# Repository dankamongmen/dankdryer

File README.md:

<p align="center">
ESP32, OpenSCAD, and KiCad sources for the Dankdryer, the world's best filament dryer.
 
 a nick black joint
</p>

# Features

* Temperatures up to at least 150℃  when printed with proper materials.
  * Such temperatures are appropriate (necessary) for certain engineering filaments.
  * A high-temperature spool is required at these temperatures.
* Accurate weight sensing throughout to determine how much water has been exorcised.
  * Post contextless deltas to reddit in the heat of dumbass arguments! DATA, bitch!
* Slow rotation like delicious savory meat.
* Equal heating of all the spool's filament.
* Control and reporting over MQTT via WiFi.
* OTA firmware upgrades.
* Isolated hot and cool chambers, with most active equipment in the cool chamber.
* Humidity sensing and temperature sensing in both chambers.
* Entirely open source.

More info at [dankwiki](https://nick-black.com/dankwiki/index.php/Dankdryer).

# Dependencies

The project is built with GNU Make.
Running `make` in the toplevel will attempt to build firmware and STLs.
Building the firmware requires the `esp-idf` library and a configured
ESP-IDF environment (i.e. the various `IDF_*` environment variables
must be set), along with CMake. `idf.py` ought be in your `$PATH`,
and work when invoked.

## Firmware
* [esp-idf](https://github.com/espressif/esp-idf) 5.3+
* [CMake](https://gitlab.kitware.com/cmake/cmake) 3.16+

## 3D models
* OpenSCAD 2024.10+

I use
[BOSL2](https://github.com/BelfrySCAD/BOSL2), which
is included as a submodule.

## PCB
* KiCad 8+

# Construction / BOM

The device as designed requires approximately 600g of high-temperature filament
(PA6-CF, PA6-GF, PAHT-CF, etc.) to print. The exact amount of filament will
depend on material and print settings. Six pieces must
be printed:

 * Hot chamber
 * Cool chamber
 * Top
 * Motor sheath
 * Sheath coupling
 * Spool platform

The hot and cool chamber dominate filament consumption, though the top is
non-negligible.

### Hot chamber

* [230C 110V ceramic heating element](https://www.amazon.com/dp/B0BXNPXXYW)
* [KSD301 175C NC thermal control](https://www.aliexpress.us/item/2251832675942217.html)
* [Hall sensor](https://www.digikey.com/en/products/detail/diodes-incorporated/AH3712Q-P-B/19920700)
* Custom PCB (fabrication cost is negligible; see components below)

We need a temperature sensor and hall effect sensor (and obviously the
heating circuit) in the hot box; nothing else ought be there.

### Cool chamber

* [Greartisan 5RPM 12V DC motor](https://www.amazon.com/dp/B072N867G3/)
* [NEMA plug + rocker switch](https://www.amazon.com/ASHATA-Rocker-Switch-Adapter-Printer/dp/B085VSS1F2)
* [160W 12V AC adapter](https://www.amazon.com/gp/product/B0D7GMVK2F)
* [8dBi antenna](https://www.aliexpress.us/item/3256807262687553.html)
* 5kg bar strain load cell
* 2-to-4 cable splitter
* Custom PCB (fabrication cost is negligible; see components below)

#### PCB components

Generated via Kicad:

|Designator|Footprint|Quantity|Designation|
|----------|---------|--------|-----------|
|U1|TPS62132|1|TPS62132|
|R4|R_1206_3216Metric_Pad1.30x1.75mm_HandSolder|1|360|
|R2|R_1206_3216Metric_Pad1.30x1.75mm_HandSolder|1|620|
|R6,R8|R_1206_3216Metric_Pad1.30x1.75mm_HandSolder|2|4.7k|
|C15,C16|C_1206_3216Metric_Pad1.33x1.80mm_HandSolder|2|1n|
|SW2|SW_B3F-1000_OMR|1|bootmode|
|R13,R20,R15|R_1206_3216Metric_Pad1.30x1.75mm_HandSolder|3|10k|
|R5,R1,R22|R_1206_3216Metric_Pad1.30x1.75mm_HandSolder|3|680|
|C7,C3,C9,C8,C20|C_1206_3216Metric_Pad1.33x1.80mm_HandSolder|5|0.1u|
|U2|TRANS_AH3712-P-B_DIO|1|AH3712Q-P-B|
|C6,C13|C_1206_3216Metric_Pad1.33x1.80mm_HandSolder|2|22u|
|C10,C17|C_1206_3216Metric_Pad1.33x1.80mm_HandSolder|2|1u|
|IC1|DIP792W51P254L1905H53Q16N|1|NAU7802KGI|
|J10|FanPinHeader_1x04_P2.54mm_Vertical|1|lower fan|
|C19,C2,C1,C14|C_1206_3216Metric_Pad1.33x1.80mm_HandSolder|4|10u|
|J2|JST_VH_B5P-VH-B_1x05_P3.96mm_Vertical|1|to microboard|
|J4|TerminalBlock_bornier-2_P5.08mm|1|heater|
|J8|TerminalBlock_bornier-2_P5.08mm|1|motor|
|J7|FanPinHeader_1x04_P2.54mm_Vertical|1|upper fan|
|R9,R19|R_1206_3216Metric_Pad1.30x1.75mm|2|15k|
|U6|XCVR_ESP32-C6-MINI-1U-H4|1|ESP32-C6-MINI-1U|
|J11|PinHeader_1x01_P1.00mm_Vertical|1|testpin|
|R16|R_1206_3216Metric_Pad1.30x1.75mm_HandSolder|1|412|
|J13|BarrelJack_Wuerth_6941xx301002|1|barreljack|
|R7|R_1206_3216Metric_Pad1.30x1.75mm_HandSolder|1|1.62k|
|C4,C18|C_1206_3216Metric_Pad1.33x1.80mm_HandSolder|2|.01u|
|J5|TerminalBlock_bornier-4_P5.08mm|1|5kg load cell|
|R10,R11|R_0805_2012Metric_Pad1.15x1.40mm_HandSolder|2|47|
|U5|TO-92_Inline|1|LM35-LP|
|R3|R_1206_3216Metric_Pad1.30x1.75mm_HandSolder|1|100|
|L1|IND_IFSC_1515AH_VIS|1|2.2u|
|R14|R_1206_3216Metric_Pad1.30x1.75mm_HandSolder|1|3.3k|
|OC1|MOC306XS_LTO|1|MOC3063S|
|C12|C_1206_3216Metric_Pad1.33x1.80mm_HandSolder|1|3.3n|
|C11|C_0805_2012Metric_Pad1.18x1.45mm_HandSolder|1|470p|
|R21|R_1206_3216Metric_Pad1.30x1.75mm_HandSolder|1|68|
|J9|PinHeader_1x04_P2.54mm_Vertical|1|UART|
|J6|JST_PHD_B8B-PHDSS_2x04_P2.00mm_Vertical|1|LCD|
|J3|JST_VH_B5P-VH-B_1x05_P3.96mm_Vertical|1|to baseboard|
|Q3|TO-263-2|1|T1210-800G|
|Q2|SOT-323_SC-70|1|SSM3K127TU|
|R12|R_1206_3216Metric_Pad1.30x1.75mm_HandSolder|1|330|
|U3|SOT-89-3|1|HT7550|

# MQTT

MQTT is used to report status and to accept commands.

## Controls

* `NAME/control/tare`: tare using the last weight read
* `NAME/control/dry`: takes as argument a string "DRYS/TEMP", where DRYS and TEMP are unsigned integers
    specifying the number of seconds to dry, and the temperature to dry at. Any ongoing drying operation
    will be replaced with the newly specified one. Specifying zero for DRYS will cancel any ongoing
    drying operation.
* `NAME/control/lpwm`: takes as argument a hexadecimal number between 0 and 255, left-padded with zeroes
    so as to be exactly two digits, i.e. "00".."ff". Sets the lower fan's PWM.
* `NAME/control/upwm`: takes as argument a hexadecimal number between 0 and 255, left-padded with zeroes
    so as to be exactly two digits, i.e. "00".."ff". Sets the upper fan's PWM.
* `NAME/control/factoryreset`: takes no arguments. Blanks the persistent storage, disables the motor
    and heater, and reboots.

# Renderings

View from the top of the lower chamber by itself, with the AC
adapter and motor assembly present.

Combined OpenSCAD render for mating testing.

# Questions

* How does air flow? Let's get some visible air and test it.
* What all could we accomplish by reading RFID?

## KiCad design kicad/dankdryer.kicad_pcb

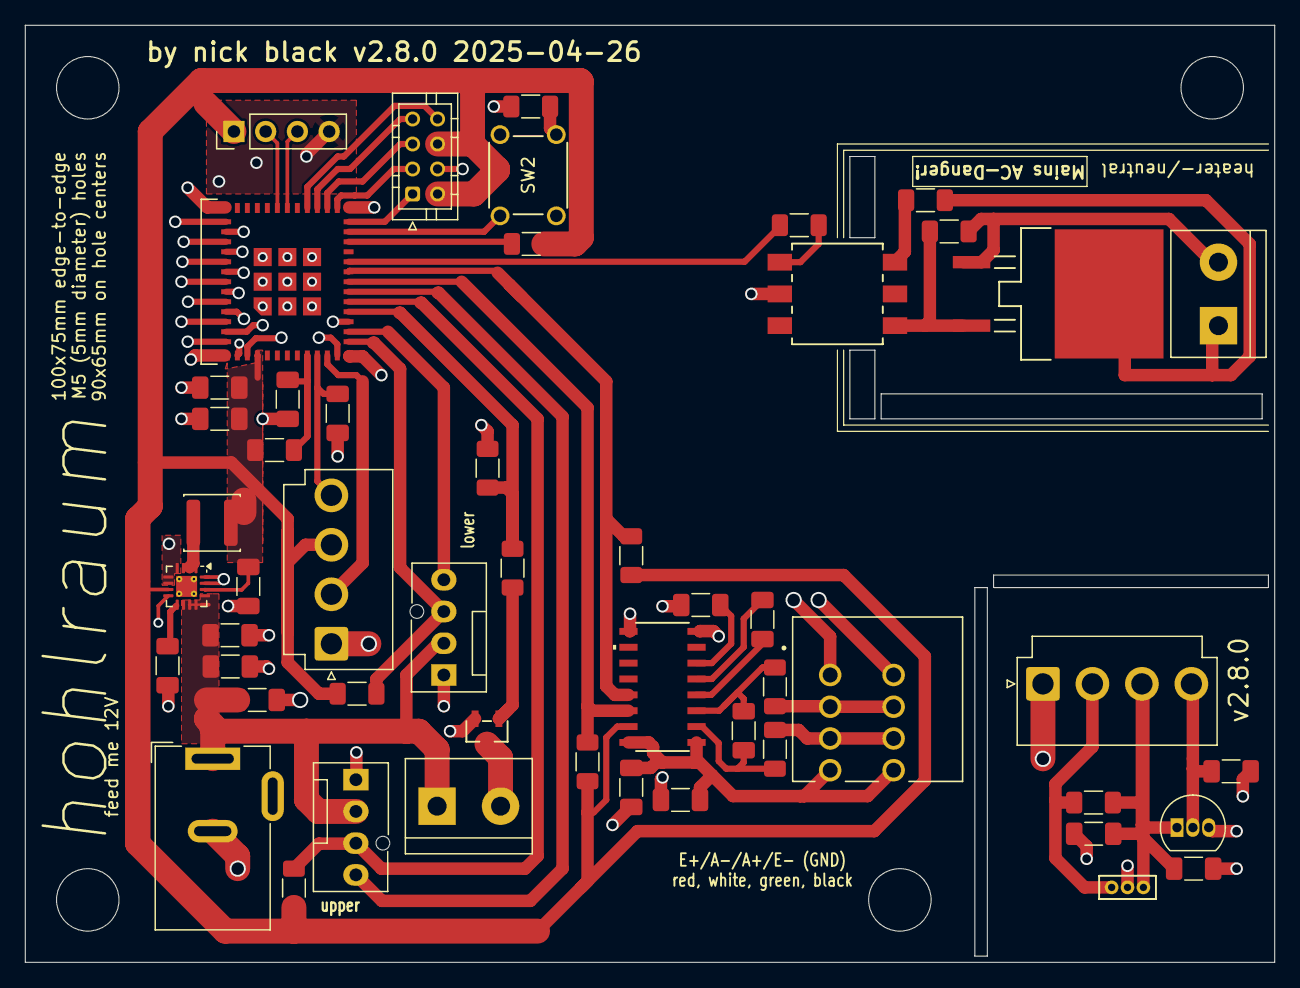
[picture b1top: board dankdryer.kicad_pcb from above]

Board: 2 copper layers, 100.0 x 75.0 mm, 52 parts (0 on the bottom side), 44 nets.

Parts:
C1, C14, C19: 10u; C_1206_3216Metric_Pad1.33x1.80mm_HandSolder
C2, C3, C5, C8, C9, C20: 100n; C_1206_3216Metric_Pad1.33x1.80mm_HandSolder
C4: 10n; C_1206_3216Metric_Pad1.33x1.80mm_HandSolder
C6, C21: 22u; C_1206_3216Metric_Pad1.33x1.80mm_HandSolder
C7: 3.3n; C_1206_3216Metric_Pad1.33x1.80mm_HandSolder
C10, C12, C17: 1u; C_1206_3216Metric_Pad1.33x1.80mm_HandSolder
C11: 330p; C_1206_3216Metric_Pad1.33x1.80mm_HandSolder
D1: T1210-800G-TR
J1: 1-2834016-4; TE_1-2834016-4
J2: to microboard; JST_VH_B4P-VH-B_1x04_P3.96mm_Vertical
J3: to baseboard; JST_VH_B4P-VH-B_1x04_P3.96mm_Vertical
J4, J8: ScrewX2; TerminalBlock_bornier-2_P5.08mm
J6: LCD; JST_PHD_B8B-PHDSS_2x04_P2.00mm_Vertical
J7, J10: HeaderX4; FanPinHeader_1x04_P2.54mm_Vertical
J9: UART; PinHeader_1x04_P2.54mm_Vertical
J13: barreljack; BarrelJack_Wuerth_6941xx301002
L1: 2.2u; L_Sunlord_SWPA4030S
OC1: MOC3063SM; MOC306XS_LTO
Q1: AH3712-P-B; TRANS_AH3712-P-B_DIO
Q2: IRLML2502TRPbF; IRLML2502TRPBF
R1, R5: 680; R_1206_3216Metric_Pad1.30x1.75mm_HandSolder
R2, R12: 330; R_1206_3216Metric_Pad1.30x1.75mm_HandSolder
R3: 100; R_1206_3216Metric_Pad1.30x1.75mm_HandSolder
R4: 390; R_1206_3216Metric_Pad1.30x1.75mm_HandSolder
R6, R8: 2.2k; R_1206_3216Metric_Pad1.30x1.75mm_HandSolder
R7, R13, R15, R20: 10k; R_1206_3216Metric_Pad1.30x1.75mm_HandSolder
R10, R11: 47; R_1206_3216Metric_Pad1.30x1.75mm_HandSolder
R14: 3.3k; R_1206_3216Metric_Pad1.30x1.75mm_HandSolder
SW2: boot; SW_B3F-1000_OMR
U3: NAU7802SGI; SOI16_NAU7802SGI_NUV
U4: TPS62132RGTR; VQFN-16-1EP_3x3mm_P0.5mm_EP1.68x1.68mm_ThermalVias
U5: LMT87LPM; TO-92_Inline
U6: ESP32-C6-MINI-1U; ESP32-C6-MINI-1U-H4

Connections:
+3.3V: C3.1, C6.2, C21.1, J2.3, J6.2, J6.6, J9.1, L1.2, R1.1, R5.1, R6.1, R8.1, R13.1, R15.1, U3.15 (DVDD), U4.7 (FSW), U4.14 (VOS), U6.3 (3V3)
+3.3Vmicro: C4.2, C19.2, J3.3, Q1.1 (VDD), R20.1, U5.1 (+V_{S})
+12V: C1.1, C2.2, C14.1, J7.2, J8.1, J10.2, J13.1, U4.10 (AVIN), U4.11 (PVIN), U4.12 (PVIN__1), U4.13 (EN)
/ACNeutral: D1.1 (A1), J4.2, R4.2
/BootDown: R15.2, U6.22 (IO8)
/BootSPI: SW2.1, U6.23 (IO9)
/Hall: J2.2, U6.10 (IO5)
/HeaterNeutral: D1.3 (A2), J4.1, R3.2
/LPWM: J10.4, U6.13 (IO1)
/LTach: J10.3, R5.2, U6.12 (IO0)
/Microboard/HallMicro: J3.2, Q1.3 (OUTPUT), R20.2
/Microboard/ThermMicro: C17.2, J3.4, U5.2 (V_{OUT})
/Motor: R7.1, R12.1, U6.15 (IO6)
/RXD0: J9.3, U6.30 (RXD0)
/SCL: R6.2, U3.13 (SCLK), U6.19 (IO14)
/SDA: R8.2, U3.14 (SDIO), U6.18 (IO13)
/SSRControl: R2.2, U6.20 (IO15)
/TXD0: J9.2, U6.31 (TXD0)
/Therm: C20.1, J2.4, U6.9 (IO4)
/UPWM: J7.4, U6.17 (IO12)
/UTach: J7.3, R1.2, U6.16 (IO7)
A+: J1.2_1 (2), J1.2_2 (2__1), R11.1
A-: J1.3_1 (3), J1.3_2 (3__1), R10.1
E+: C5.1, C12.1, J1.4_1 (4), J1.4_2 (4__1), U3.1 (REFP), U3.16 (AVDD/LDO)
GND: C1.2, C2.1, C3.2, C4.1, C5.2, C6.1, C7.2, C8.2, C10.2, C12.2, C14.2, C17.1, C19.1, C20.2, C21.2, J1.1_1 (1), J1.1_2 (1__1), J2.1, J3.1, J6.4, J7.1, J9.4, J10.1, J13.2, OC1.2 (C), Q1.2 (GND), Q2.2 (S), R7.2, R14.2, U3.8 (AVSS), U3.9 (DVSS), U4.4 (PG), U4.5 (FB), U4.6 (AGND), U4.8 (DEF), U4.15 (PGND), U4.16 (PGND__1), U4.17 (PGND__2), U5.3 (GND), U6.1 (GND1), U6.2 (GND1), U6.11 (GND1), U6.14 (GND1), U6.36 (GND1), U6.37 (GND1), U6.38 (GND1), U6.39 (GND1), U6.40 (GND1), U6.41 (GND1), U6.42 (GND1), U6.43 (GND1), U6.44 (GND1), U6.45 (GND1), U6.46 (GND1), U6.47 (GND2), U6.48 (GND2), U6.49_1 (GND2), U6.49_2 (GND2), U6.49_3 (GND2), U6.49_4 (GND2), U6.49_5 (GND2), U6.49_6 (GND2), U6.49_7 (GND2), U6.49_8 (GND2), U6.49_9 (GND2), U6.50 (GND2), U6.51 (GND2), U6.52 (GND2), U6.53 (GND2)
LCDCS: J6.8, U6.28 (IO22)
LCDDC: J6.7, U6.27 (IO21)
LCDRst: J6.1, U6.24 (IO18)
LCDSCL: J6.3, U6.25 (IO19)
LCDSDA: J6.5, U6.26 (IO20)
unnamed: D1.2 (G), OC1.4 (MT1), R4.1
unnamed: J8.2, Q2.3 (D)
unnamed: OC1.1 (A), R2.1
unnamed: OC1.6 (MT2), R3.1
unnamed: Q2.1 (G), R12.2
unnamed: R14.1, SW2.4
unnamed: C8.1, U3.6 (VBG)
unnamed: C9.1, R10.2, U3.2 (VIN1N)
unnamed: C9.2, R11.2, U3.3 (VIN1P)
unnamed: C11.1, U3.4 (VIN2N)
unnamed: C11.2, U3.5 (VIN2P)
unnamed: C7.1, U4.9 (SS/TR)
unnamed: L1.1, U4.1 (SW), U4.2 (SW__1), U4.3 (SW__2)
unnamed: C10.1, R13.2, U6.8 (EN)

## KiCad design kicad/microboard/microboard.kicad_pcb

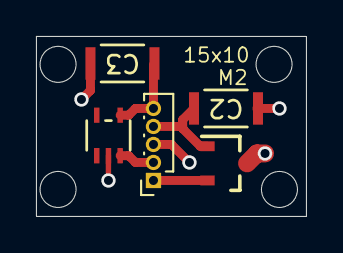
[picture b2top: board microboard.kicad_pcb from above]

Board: 2 copper layers, 15.0 x 10.0 mm, 5 parts (0 on the bottom side), 5 nets.

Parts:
C2: .01u; CAP_3216_TDK
C3: .1u; CAP_3216_TDK
J2: Conn_01x05_Socket; PinSocket_1x05_P1.00mm_Vertical
U1: TMP235A4DCKR; DCK5_TEX
U2: DRV5011ADDBZR; DBZ0003A_L

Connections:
/+3.3V: C2.2, J2.4, U2.1 (VCC)
/+5VA: C3.1, J2.5, U1.4 (VDD)
/Hall: J2.1, U2.2 (OUT)
/ThermAnalog: J2.2, U1.3 (VOUT)
GND: C2.1, C3.2, J2.3, U1.2 (GND), U2.3 (GND)

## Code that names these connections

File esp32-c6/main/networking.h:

#ifndef DANKDRYER_NETWORKING
#define DANKDRYER_NETWORKING

#include <nvs.h>
#include <stddef.h>
#include <stdint.h>
#include <stdbool.h>
#include <soc/gpio_num.h>

int setup_network(void);
int handle_dry(unsigned sec, unsigned temp);
int extract_bool(const char* data, size_t dlen, bool* val);
int extract_pwm(const char* data, size_t dlen);
void set_motor(bool enabled);
void set_lower_pwm(unsigned pwm);
void set_upper_pwm(unsigned pwm);
unsigned get_lower_pwm(void);
unsigned get_upper_pwm(void);
unsigned get_lower_rpm(void);
unsigned get_upper_rpm(void);
uint32_t get_spool_rpm(void);
float get_weight(void);
float get_tare(void);
float get_upper_temp(void);
float get_lower_temp(void);
unsigned long long get_dry_ends_at(void);
unsigned long get_target_temp(void);
bool get_motor_state(void);
bool get_heater_state(void);
void set_tare(void);
void factory_reset(void);
void mqtt_publish(const char *s);
int write_wifi_config(const unsigned char* essid, const unsigned char* psk,
                      uint32_t state);
int read_wifi_config(unsigned char* essid, size_t essidlen,
                     unsigned char* psk, size_t psklen,
                     int* setupstate);
int read_mqtt_config(char** broker, char** user, char** pass,
                     char** topic);

#define CCHAN "control/"
#define MOTOR_CHANNEL CCHAN DEVICE "/motor"
#define HEATER_CHANNEL CCHAN DEVICE "/heater"
#define LPWM_CHANNEL CCHAN DEVICE "/lpwm"
#define UPWM_CHANNEL CCHAN DEVICE "/upwm"
#define OTA_CHANNEL CCHAN DEVICE "/ota"
#define DRY_CHANNEL CCHAN DEVICE "/dry"
#define TARE_CHANNEL CCHAN DEVICE "/tare"
#define CALIBRATE_CHANNEL CCHAN DEVICE "/calibrate"
#define FACTORYRESET_CHANNEL CCHAN DEVICE "/factoryreset"

#endif

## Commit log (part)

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2024-12-25 README: embrace hotbox microboard
2024-12-26 kicad: note about AVDD on NAU7802
2024-12-26 esp32: remove dross from CMakeFiles
2024-12-26 rename emc2302 -> emc230x
2024-12-26 setup_emc2302: call emc230x_detect()
2024-12-26 use esp-idf component for emc230x
2024-12-26 kicad: pcb v0.99
2024-12-26 470pf capacitor on VI2N + VI2P
2024-12-26 esp: write fan pwms via emc2302
2024-12-26 esp: use emc230x_gettach() to read fan tachometers
2024-12-26 symlink dependencies.lock
2024-12-26 keep real dependencies.lock in -s3
2024-12-26 blockdiagram: replace relay with mosfet
2024-12-26 s/lprm/lrpm/g
2024-12-26 ignore kicad .rpt files
2024-12-27 add setup_nau7802() to startup sequence
2024-12-28 streamline clean target
2024-12-29 TPU interlayer #75
2024-12-29 add interlayer to webpage #75
2024-12-29 pull some obsolete images
2024-12-29 README: mention interlayer, closes #75
2024-12-29 scad: screw-in locking top via BOSL2's threaded_rod() #8
2024-12-29 kicad: document T1210 holding/latching currents
2024-12-29 update microboard for current 5-pin connector
2024-12-29 get hall sensor count along with fan tachs #68
2024-12-29 add spool rpm to mqtt / http #68
2024-12-31 webpage: mention AC shield
2024-12-31 webpage: make it clear that the interlayer is optional
2024-12-31 webpage: list contents of kit
2024-12-31 specify fans
2024-12-31 get off the strapping pins. hardware version 1.0
2024-12-31 webpage: update copyrights
2025-01-05 replace NAU7802SGI with NAU7802KGI i accidentally bought
2025-01-05 add 0.1uf capacitor to ADC input line closes #78
2025-01-05 sdkconfig changes
    * disable DHCP server
    * enable pulling NTP from DHCP
    (see #52; this got reverted somehow)
    * provide a fallback DNS server using 8.8.8.8
2025-01-05 support both preconfigured and DHCP NTP servers #77
2025-01-07 update to v1.0.2 of emc230x driver
2025-01-09 upgrade to emc230x 1.0.4 and mdns 1.4.3
2025-01-09 beefier capacitors on the microboard
2025-01-14 clean up silkscreen a little
2025-01-14 reverse scl/sda pins
2025-01-14 belay that pin change
2025-01-19 enable openthread in sysconfig #81
2025-01-19 add component openthread #81
2025-01-19 call esp_openthread_init()
2025-01-21 error on warning
2025-01-21 switch from 1A to 3A TPS62132 for 3.3V
2025-01-22 eliminate emc2302 #84
2025-01-23 [sdkconfig] updates for new esp-idf
2025-01-23 update pin definition to restore direct fan control #84
2025-01-23 [pcb] drop inductor reference text
2025-01-23 use new ledc_set_duty_and_update() to combine two calls
2025-01-30 first stab at auto pcb render
2025-01-30 add lcd initialization code
2025-01-31 mounts for LCD
2025-02-05 [croom] cut bottom corners on shears to fight warping #89
2025-02-07 [croom] much improved rounding of bottom #89
2025-02-07 kill wirechannels, tighten croom bottom
2025-02-07 webpage: bye banner
2025-02-08 [hotbox] kill rc522 holes for now
2025-02-11 move vcuts to user.1
2025-02-11 [hotbox] round bottom corners, shrink connectors
2025-02-11 [croom] adapt to 80mm load cell #90
2025-02-11 [coupling] restore necessary constants
2025-02-11 [croom] adapt to new ac adapter geometry
2025-02-11 [coupling] adapt to 80mm load cell #90
2025-02-11 [coupling] punch hole through coupling for inner load cell screw
2025-02-12 [coupling] m5s throughout load cell coupling
2025-02-12 [croom] tighten antenna hole
2025-02-14 [hotbox] remove hbcorners
2025-02-14 makefile: remove interlayer build
2025-02-14 [kicad] fix 3dmodel for JST-VH-B5P connectors
2025-02-14 workflow: upgrade to upload_artifactv4
2025-02-14 [pcb] synchronize jst-vh-b5b connectors
2025-02-14 use deploy-pages@v4
2025-02-14 [webpage] move assembly to its own page
2025-02-14 [webpage] use h3 for assembly link
2025-02-14 [webpage] link to assembly.html from top
2025-02-14 v1.5.1
2025-02-14 v1.5.1 pcb
2025-02-16 update to 1206 where appropriate
2025-02-16 tighten ScrewThreads
2025-02-16 remove lcd panel for now
2025-02-18 1.7.2: move fan capacitors to 1206
2025-02-18 disable OpenThread and HTTPS client to save space
2025-02-18 add external antenna STL
2025-02-18 complete.scad: fix colors
2025-02-18 remove emc2302 code
2025-02-18 promote R11 to 1206
2025-02-21 invert logic for gpio9, erp
2025-02-21 switch from AKL_R to regular
2025-02-21 kill quotation marks in BOM
2025-02-21 remove obsolete comment
2025-02-24 add ignores
2025-02-24 kill offcard project
2025-02-24 kill microboard
2025-02-24 make images by default
2025-02-24 ignore production output
2025-02-24 Revert "kill microboard"
    This reverts commit e7a6377caa4ae73bc4ee8e255010d285ca4e6727.
2025-02-24 don't build images in CI
2025-02-24 make interrupt variables _Atomic(uint32_t)
2025-02-24 pulse_isr: cast to atomic from void* munge
2025-02-26 upgrade to kicad9
2025-02-26 extend the top screw
2025-02-26 disable pcb_image workflow for now
2025-02-26 [scad] expand pitch for joiners
2025-02-26 [top] fix bug that led to overprinting top surface
2025-02-26 no more polycarbonate
2025-02-26 [webpage] no more bambu clear black pc
2025-02-28 move to mounting rods from holes for PCB #92
2025-02-28 conver ac adapter mounting holes to mounting rods #92
2025-02-28 M4 mounting rods for ac adapter
2025-02-28 [croom] no levitating mount rods
2025-02-28 use core height of 81 instead of 80, to divide evenly by 0.3
2025-02-28 [core] use ScrewThread for more precise fan holes
2025-02-28 [croom] taller threads to accept locknuts #98
2025-02-28 [croom] thread tops of ac adapter mounts #98
2025-02-28 [hotbox] thread mounting rods for locknuts #98
2025-02-28 [croom] publicize acadapter() and pcb()
2025-02-28 don't try to query NAU if we couldn't initialize it
2025-03-01 bluetooth gatt tool
2025-03-01 [croom] use 70 rounding at top #96
2025-03-01 [hotbox] kill unused cornerscrew code #96
2025-03-01 [core] introduce midcantis #96
2025-03-01 [croom] midcantis for croom #96
2025-03-02 try friction fit circular plug #96
2025-03-04 [miniboard] throughholes need [5, -5] separation #99
2025-03-04 chamber clips #96
2025-03-04 [webpage] full MQTT topic descriptions
2025-03-04 [models] six chamber clips
2025-03-04 [models] croomclips on all four sides
2025-03-04 change DEVICE to hohlraum
2025-03-04 webpage: s/Dankdryer/Hohlraum/g
2025-03-04 remove blockdiagram dot file
2025-03-04 call ledc_fade_func_install(). call setup_adc_oneshot() after setup_temp()
2025-03-04 [hotbox] raise ceramheat unthreaded rods
2025-03-04 [core] give some skoosh on chamber clips
2025-03-04 [pcb] tighten it up, keep things away from miniboard
2025-03-05 v1.9.1, no more crossing of triac pads
2025-03-05 [adc] remove bogon Thermchan initialization
2025-03-06 [scad] move chamber clips to internal side
2025-03-08 tighten
2025-03-08 back to the tps62132rtgr after all. efficiency!
2025-03-08 VERSION=1.9.8
2025-03-08 [hotbox] add some height to fit fan
2025-03-08 use 30 degree slope underpinning chamber plugs
2025-03-09 upgrade to espressif mdns 1.8.0
2025-03-10 [scad] move mount() to common, use it for heater mounts in hotbox
2025-03-10 [hotbox] 3.3mm for heater plugs
2025-03-10 [scad] update exported pcb
2025-03-12 [models] more skoosh on couplings for nylon
2025-03-12 move gpio static inlines to pins.h
2025-03-12 move all fan-related code to fans.c
2025-03-12 [scad] drop extra param to platform()
2025-03-12 [makefile] generate open.png using complete.scad + OPENTOP decl
2025-03-12 [pcb] expand use of zones
2025-03-12 [makefile] fix stl build
2025-03-12 use nau7802 0.1.0, explicitly call nau7802_set_pga_cap()
2025-03-12 [croom] use basic cylinders for ac adapter
2025-03-14 [kicad] tighten things up
2025-03-14 [core] use autoselect for threading in mount()
2025-03-14 add m[45]nutlocks
2025-03-14 [hotbox] angle the ptfe tube up at 45deg #102
2025-03-14 [scad] don't place outer tabs immediately opposite inner tabs
2025-03-16 [corescad] decrease thread pitch for topmate
2025-03-16 [croom] use mount() for acadapter mounts
2025-03-16 add hooks for factory reset handling #69
2025-03-16 implement check_hardware_reset() #69
2025-03-16 call check_factory_reset() from app_main() loop #69
2025-03-16 change 330 ohm resistors to 1206
2025-03-17 add corner plugs #103
2025-03-18 [pcb] swap mosfet inputs
2025-03-24 webpage: we're droppin' prices!
2025-03-24 put your boot down
2025-03-24 [kicad] drop Cfilter from 470 pF to 330 pF
2025-03-24 try to initialize nau7802 on each loop
2025-03-24 slightly widen antenna hole
2025-03-26 update espressif subcomponents
2025-03-26 move to 2.2k resistors for I2C
2025-03-26 sync pin definitions to reality, fixes nau7802 detection yay
2025-03-26 fix swapped upper fan pins
2025-03-26 lift scaling calculation out of getPulseCount()
2025-03-27 v2.1.5
2025-03-28 switch orientation of antenna hole #106
2025-03-29 kill RC low pass filter on tachometers
2025-03-30 [nau7802] link avdd to refp, add capacitors #108
2025-03-30 enable 3.3V LDO on NAU7802
2025-03-31 nau7802 version 0.2.0
2025-03-31 update config for cutting edge esp-idf
2025-03-31 nau7802 0.2.2
2025-04-05 subscribe to heater control channel
2025-04-05 pins: switch hall and them
2025-04-07 don't run heater without a hot chamber temp
2025-04-07 move heater code to its own file
2025-04-07 [efuse] load serial number / product id from eFuse #107
2025-04-07 incorporate serial number into hostname/mDNS/BLE #107
2025-04-07 [efuse] distinguish between electronics versions using device ID #109
2025-04-07 [ble] add characteristic to set device ID on factory init #107
2025-04-07 [efuse] validate device id received over BLE #107
2025-04-07 [efuse] encode device id received over BLE and write to efuse #107
2025-04-07 [kicad] heater circuit sub
2025-04-07 [mdns] use constructed clientID #107
2025-04-07 install an interrupt handler on the button pin #69
2025-04-07 enable pullup on GPIO9, disable pulldown
2025-04-07 [kicad] remove mention of GPIO18
2025-04-07 define attempt_ota()
2025-04-08 [pcb] eliminate voltage divider before ltach closes #112
2025-04-09 [scad] move ac adapter into its own file
2025-04-09 [heater] use esp-log
2025-04-09 consolidate thermals in heater.c
2025-04-09 [pcb] label load cell hookups
2025-04-11 add clips for IEC plug, closes #113
2025-04-11 models v2.2.1
2025-04-13 kicad/scad v2.2.2
2025-04-13 preserve bootcount across a factory reset
2025-04-13 v2.2.2
2025-04-17 convert all stderr to ESP_LOGE
2025-04-17 convert more printfs to esp logging
2025-04-17 move NAU7802 capacitors
2025-04-19 use nau7802 driver 0.3.2
2025-04-19 use nau7802_read_scaled(), fixes load cell sampling i think
2025-04-21 [nau7802] disable bandwidth chopper
2025-04-21 use nau7802_multisample()
2025-04-21 use esp logging for ADC read
2025-04-21 don't use nau7802_multisample()
2025-04-21 kill newline
2025-04-27 [kicad] move to spring clips for load cell
2025-04-27 [scad] rotate plug, sink bolts in lower coupling
2025-04-28 [croom] flare bottom of loadcellmount more
2025-05-01 [pcb] fatten a few traces
2025-05-07 put in 3dsymbol for buck converter
2025-05-07 give IEC plug some skoosh in the long dimension
2025-05-13 skoosh it forward
2025-05-13 update sdkconfig for newer esp-idf
2025-05-13 implement and call write_mqtt_config() #116
2025-05-13 [networking] add all 4 characteristics for MQTT #116
2025-05-13 remove dryer-network.h mention from README.md
2025-05-13 [workflow] remove dryer-network.h operation
2025-05-13 call reconfig_mqtt() in setup_networking()
2025-05-13 expand chamberclipinverse skoosh
2025-05-15 [networking] handle empty mqtt config to cancel mqtt client
2025-05-15 [networking] factor out ble_accept_characteristic()
2025-05-16 define mqttconfig helper struct, rewrite NVS MQTT in terms of it
2025-05-16 add mqttconfig_free(), use it in read_mqttconfig() error path
2025-05-22 [BLE] don't allow MQTT broker without MQTT topic
2025-05-22 use esp-idf 6.0.0+
